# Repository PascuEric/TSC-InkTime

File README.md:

# InkTime — Smartwatch

InkTime is an open-source, minimalist smartwatch built around an always-readable 1.54" e-paper display and optimized for month-class battery life (≥30 days on a 250 mAh LiPo). It features BLE 5.0 notifications, embedded step counting, haptic alerts, and USB-C charging.

---

## Block Diagram

```
                          ┌──────────────────────────────────────────┐
         USB-C            │           nRF52840 (U1)                  │
        ──────►──┐        │                                          │
                 │  VBUS  │  ┌─────────────────────────────────┐     │
                 ▼        │  │         I2C Bus                 │     │
          ┌──────────┐    │  │  SDA P0.06 / SCL P0.07          │     │
          │ BQ25180  │◄───┼──┤  Pull-up 3K3 to 3V3             │     │
          │  (IC1)   │    │  │                                 │     │
          │ Charger  │    │  │  BQ25180 (0x6A)  RT6160 (0x75)  │     │
          └────┬─────┘    │  │  MAX17048 (0x36) BMA421 (0x18)  │     │
               │ SYS      │  │  DRV2605L (0x5A)                │     │
          ┌────▼─────┐    │  └─────────────────────────────────┘     │
          │ RT6160   │◄───┤                                          │
          │  (IC9)   │    │  ┌─────────────────────────────────┐     │
          │Buck-Boost│    │  │        SPI Bus                  │     │
          └────┬─────┘    │  │  SCK P0.02 / MOSI P0.03         │     │
               │ 3V3      │  │  CS P0.05 / DC P0.15            │     │
               ▼          │  │  RST P0.16 / BUSY P0.17         │     │
    ┌──────────────────┐  │  │  PFET gate P1.01                │     │
    │   3V3 Power Rail │  │  │                                 │     │
    └─┬───┬───┬───┬────┘  │  │  E-Paper 1.54" 200x200 (J1)     │     │
      │   │   │   │       │  │  via SI1308EDL MOSFET (Q3)      │     │
      │   │   │   │       │  └─────────────────────────────────┘     │
      │   │   │   │       │                                          │
      │   │   │   │       │  GPIO                                    │
      │   │   │   └───────┼──► SW_UP P0.13 / SW_DN P0.14             │
      │   │   │           │    SW_ENT P1.00                          │
      │   │   │           │  INT: BMA421 INT1→P0.08 INT2→P1.08       │
      │   │   │           │       MAX17048 ALRT→P0.10                │
      │   │   │           │       BQ25180 /INT→P0.11                 │
      │   │   │           │       HAPTIC_EN→P0.12                    │
      │   │   │           │                                          │
      │   │   │           │  RF: ANT→L1(3.9nH)→L3(15nH)→ANT1         │
      │   │   │           │  USB: D+/D-→USBLC6(D3)→USB-C (J4)        │
      │   │   │           │  SWD: SWDIO/SWDCLK/RESET→TC2030 (J2)     │
      │   │   │           └──────────────────────────────────────────┘
      │   │   │
      │   │  ┌▼────────────┐    ┌──────────────┐
      │   │  │  DRV2605L   ├───►│  ERM Motor   │
      │   │  │  (IC2) I2C  │    │  (Haptic)    │
      │   │  └─────────────┘    └──────────────┘
      │   │
      │  ┌▼────────────┐
      │  │   BMA421    │
      │  │   (IC3) I2C │  INT1→P0.08 / INT2→P1.08
      │  └─────────────┘
      │
     ┌▼────────────┐
     │  MAX17048   │
     │  (U3) I2C   │  ALRT→P0.10
     └─────────────┘

  ┌──────────┐
  │  LiPo    │──VBAT──► BQ25180 (BAT) ──► MAX17048 (BAT/VDD)
  │ 250 mAh  │
  └──────────┘
```

---

## Bill of Materials (BOM)

| Qty | Ref | Component | Package | Description | JLCPCB | Datasheet |
|-----|-----|-----------|---------|-------------|--------|-----------|
| 1 | U1 | nRF52840-QIAA-R | aQFN73 | MCU BLE 5.0 + USB 2.0 | — | [Link](https://infocenter.nordicsemi.com/pdf/nRF52840_PS_v1.7.pdf) |
| 1 | IC1 | BQ25180YBGR | DSBGA-8 | LiPo charger / power path | [C3682423](https://jlcpcb.com/partdetail/TexasInstruments-BQ25180YBGR/C3682423) | [Link](https://www.ti.com/lit/ds/symlink/bq25180.pdf) |
| 1 | IC9 | RT6160AWSC | WLCSP-15 | Buck-boost 3.3V regulator | [C7065276](https://jlcpcb.com/partdetail/Richtek-RT6160AWSC/C7065276) | [Link](https://www.richtek.com/assets/product_file/RT6160A/DS6160A-00.pdf) |
| 1 | U3 | MAX17048G+T10 | DFN-8 | Fuel gauge I2C | — | [Link](https://datasheets.maximintegrated.com/en/ds/MAX17048-MAX17049.pdf) |
| 1 | IC3 | BMA421 | LGA-12 | Accelerometer + step counter | — | [Link](https://www.bosch-sensortec.com/media/boschsensortec/downloads/datasheets/bst-bma421-ds000.pdf) |
| 1 | IC2 | DRV2605YZFR | DSBGA-9 | Haptic driver ERM/LRA | — | [Link](https://www.ti.com/lit/ds/symlink/drv2605l.pdf) |
| 1 | Q3 | SI1308EDL-T1-GE3 | SC-70 | N-ch MOSFET EPD power gate | — | [Link](https://www.vishay.com/docs/63587/si1308edl.pdf) |
| 1 | DMG2305UX-7 | DMG2305UX-7 | SOT-23 | P-ch MOSFET EPD drive | — | — |
| 1 | ANT1 | 2450AT18B100E | SMD 3216 | 2.45 GHz chip antenna | — | [Link](https://www.johansontechnology.com/datasheets/2450AT18B100E/2450AT18B100E.pdf) |
| 1 | J4 | KH-TYPE-C-16P | THT | USB-C 16-pin connector | — | — |
| 1 | D3 | USBLC6-2SC6Y | SOT-23-6 | USB ESD protection | — | [Link](https://www.st.com/resource/en/datasheet/usblc6-2.pdf) |
| 3 | D2,D4,D5 | MBR0530 | SOD-123 | Schottky diode 30V 500mA | — | — |
| 1 | J2 | TC2030-IDC | PCB footprint | Tag-Connect SWD debug | — | [Link](https://www.tag-connect.com/wp-content/uploads/bsk-pdf-manager/TC2030-IDC_1.pdf) |
| 1 | J1 | 503480-2400 | FPC 24-pin | E-paper FPC connector 0.5mm | — | [Mouser](https://www.mouser.co.uk/ProductDetail/Molex/503480-2400) |
| 3 | SW_UP,SW_DN,SW_ENT | EVP-AKE31A | SMD | Tactile button Panasonic | — | — |
| 1 | X1 | 32 MHz crystal | 2016 SMD | HFXO nRF52840 | — | — |
| 1 | X2 | 32.768 kHz crystal | 3215 SMD | LFXO RTC nRF52840 | — | — |
| 1 | L7 | FTC252012SR47MBCA | 2520 | 0.47 µH RT6160 switching | [C5832368](https://jlcpcb.com/partdetail/6763488-FTC252012SR47MBCA/C5832368) | — |
| 1 | L2 | 10 µH | 0402 | RT6160 power stage | — | — |
| 1 | L3 | 15 nH | 0402 | RF matching network | — | — |
| 1 | L1 | 3.9 nH | 0402 | RF matching network | — | — |
| 1 | L5 | 68 µH | 0402 | EPD boost converter | — | — |
| 5 | C5,C7,C8,C12,C19 | 100 nF | 0201 | Decoupling nRF52840 | — | — |
| 4 | C1,C2,C17,C18 | 12 pF | 0201 | Crystal load caps | — | — |
| 6 | C29–C32,C37,C38 | 1 µF | 0201 | Bulk decoupling | — | — |
| 3 | C23,C27,C42 | 0.1 µF | 0201 | Decoupling | — | — |
| 2 | C25,C33 | 22 µF | 0402 | RT6160 output caps | — | — |
| 3 | C14,C20,C21 | 4.7 µF | 0402 | Bulk decoupling | — | — |
| 1 | C43 | 4.7 µF | 0402 | DECUSB nRF52840 | — | — |
| 1 | C24 | 10 µF | 0402 | RT6160 input cap | — | — |
| 9 | EPD_C1..C12 | 1 µF/50V | 0402 | EPD supply caps | — | — |
| 1 | C15 | 1.0 µF | 0201 | DEC4/6 nRF52840 | — | — |
| 1 | C11 | 100 pF | 0201 | RF matching | — | — |
| 2 | C3,C4 | 1 pF | 0201 | RF matching | — | — |
| 1 | C9 | 820 pF | 0201 | RF decoupling | — | — |
| 2 | R17,R18 | 3.3 kΩ | 0201 | I2C pull-ups SDA/SCL | — | — |
| 3 | R5,R7,R8 | 10 kΩ | 0201 | Button pull-ups | — | — |
| 2 | R1_USB,R2_USB | 5.1 kΩ | 0201 | USB CC1/CC2 resistors | — | — |
| 14 | TP_* | Test pad | TP20R | Test points | — | — |
| 1 | SJ1 | Solder jumper | SMD | Config jumper | — | — |

---

## Hardware Functionality Description

### Power Architecture

```
USB 5V → BQ25180 (IN) → BQ25180 (SYS) → RT6160 (VIN) → 3.3V rail
LiPo   → BQ25180 (BAT) and LiPo → MAX17048 (BAT/VDD)
```

**BQ25180 (IC1)** handles LiPo charging and power-path management. When USB is present, it powers the system from USB and charges the battery simultaneously without brownout on connect/disconnect. TS/MR strapped to GND (R9, 10kΩ) for Rev A. Decoupling: C37 (1µF on IN), C39 (10µF on SYS), C38 (1µF on BAT).

**RT6160 (IC9)** is a buck-boost maintaining stable 3.3V across the full LiPo discharge range (4.2V → 3.0V). VSEL tied low for 3.3V output. EN tied to VSYS (always on when SYS present). Switching inductor L7 (0.47µH) placed close to SW pins. Output caps C25 + C33 (22µF each).

**MAX17048 (U3)** reports battery state-of-charge over I2C (0x36) using the ModelGauge algorithm, requiring no sense resistor. ALRT output (active-low) on P0.10 wakes MCU when battery drops below threshold.

### MCU — nRF52840 (U1)

ARM Cortex-M4F, 64 MHz, BLE 5.0, USB 2.0 Full Speed. Normal-voltage mode (VDD = 3.3V). Internal DC/DC regulator (REG1) enabled in firmware to reduce active-mode current.

Decoupling placed directly at MCU pins: DEC1 → C7 (100nF), DEC3 → C8 (100nF), DEC4/DEC6 → C15 (1µF), DECUSB → C43 (4.7µF). DC/DC network: DCC → L2 (10µH) → L3 (15nH) → DEC4/6 node.

### I2C Bus

SDA P0.06 / SCL P0.07, pull-ups R17+R18 (3.3kΩ to 3V3), 100 kHz default.

| Device | Address | Function |
|--------|---------|---------|
| BMA421 (IC3) | 0x18 | Accelerometer + step counter |
| MAX17048 (U3) | 0x36 | Fuel gauge |
| DRV2605L (IC2) | 0x5A | Haptic driver |
| BQ25180 (IC1) | 0x6A | Charger / power path |
| RT6160 (IC9) | 0x75 | Buck-boost regulator |

### E-Paper Display (J1)

1.54" 200×200 e-paper via Molex 503480-2400 24-pin FPC connector (0.5mm pitch). SPI communication. VEPD switched by SI1308EDL N-ch MOSFET (Q3, gate P1.01) for complete power gating between updates. EPD boost circuit: D2, D4, D5 (MBR0530) + L5 (68µH) + DMG2305UX-7 generates PREVGL/PREVGH panel voltages. Optional DNP series resistors on SPI lines prevent back-powering when VEPD off.

### Accelerometer — BMA421 (IC3)

Embedded step counter running autonomously. I2C 0x18 (CSB high, SDO low). INT1 → P0.08 for motion/step wake; INT2 → P1.08 for secondary events. Placed away from ERM motor to avoid false motion coupling.

### Haptics — DRV2605L (IC2)

Drives ERM motor via I2C (0x5A). EN pin P0.12 shuts down driver completely between events. Built-in waveform library selectable by effect ID over I2C.

### RF — ANT1

Matching network: ANT → L1 (3.9nH) → L3 (15nH) → C3/C4 (1pF to GND) → 2450AT18B100E chip antenna. Antenna at PCB edge with physical cutout and GND keepout underneath.

### USB-C (J4)

USB 2.0 FS. D+/D- differential pair with matched lengths. USBLC6-2SC6Y (D3) ESD protection at connector entry. R1_USB + R2_USB (5.1kΩ each) on CC1/CC2 for USB-C sink detection.

### Energy Budget

| Condition | Current | Fraction | Avg µA |
|-----------|---------|----------|--------|
| Deep sleep | ~3 µA | 98.8% | ~3.0 |
| EPD partial refresh (2s/min) | ~8 mA | 0.13% | ~10.4 |
| BLE notification | ~15 mA | 0.05% | ~7.5 |
| Haptic event | ~50 mA | 0.02% | ~10.0 |
| **Total** | | | **~31 µA** |

250 mAh / 0.031 mA ≈ **~33 days** typical use.

---

## nRF52840 Pin Assignment

| Pin | Net | Dir | Connected to | Rationale |
|-----|-----|-----|-------------|-----------|
| P0.02 | SCK | OUT | EPD display | SPI — high-speed Port 0 peripheral |
| P0.03 | MOSI | OUT | EPD display | SPI data out |
| P0.05 | EPD_CS | OUT | EPD display | SPI chip select |
| P0.06 | SDA | I/O | All I2C ICs | Nordic reference I2C pin |
| P0.07 | SCL | OUT | All I2C ICs | Nordic reference I2C pin |
| P0.08 | IMU_INT1 | IN | BMA421 INT1 | GPIO sense, wake from deep sleep |
| P0.10 | ALERT | IN | MAX17048 ALRT | Low battery wake |
| P0.11 | PMIC_INT | IN | BQ25180 /INT | Charger event interrupt |
| P0.12 | HAPTIC_EN | OUT | DRV2605L EN | Haptic driver shutdown between events |
| P0.13 | SW_UP | IN | Button UP | GPIO sense + internal pull-up, wake capable |
| P0.14 | SW_DN | IN | Button DOWN | GPIO sense + internal pull-up, wake capable |
| P0.15 | EPD_DC | OUT | EPD display | Data/command select |
| P0.16 | EPD_RST | OUT | EPD display | Panel reset |
| P0.17 | EPD_BUSY | IN | EPD display | Busy status |
| P0.18/RESET | nRESET | IN | TC2030 pin 6 | Dedicated hardware reset |
| P0.00/XL1 | LFXO | — | X2 crystal | 32.768 kHz RTC |
| P0.01/XL2 | LFXO | — | X2 crystal | 32.768 kHz RTC |
| XC1/XC2 | HFXO | — | X1 crystal | 32 MHz RF/CPU |
| ANT | RF | — | L1→L3→ANT1 | Antenna matching network |
| VBUS | Detect | IN | USB-C VBUS | USB attach detection |
| D+/D- | USB | I/O | USBLC6→J4 | USB 2.0 FS differential pair |
| SWDIO | SWD | I/O | TC2030 pin 2 | Programming + debug |
| SWDCLK | SWD | IN | TC2030 pin 4 | Programming + debug |
| P1.00 | SW_ENT | IN | Button ENTER | GPIO sense + pull-up, wake capable |
| P1.01 | EPD_PWR | OUT | Q3 gate | EPD power gate control |
| P1.08 | IMU_INT2 | IN | BMA421 INT2 | Secondary accel events |
| DCC | DC/DC | — | L2 (10µH) | Internal regulator inductor |
| DEC1 | Decoupling | — | C7 (100nF) | Core decoupling |
| DEC3 | Decoupling | — | C8 (100nF) | Core decoupling |
| DEC4/DEC6 | Decoupling | — | C15 (1µF) | DC/DC output node |
| DECUSB | Decoupling | — | C43 (4.7µF) | USB PHY decoupling |

---

## PCB Design Notes

**Stackup:** 2-layer, FR4, 1.6mm. Top + Bottom copper (1oz), green soldermask, white silkscreen.

**Placement:** nRF52840 centered; RF matching + ANT1 at top-right board edge with physical PCB cutout and GND keepout under antenna; BQ25180 + RT6160 grouped away from antenna; BMA421 separated from ERM motor; all 100nF decoupling within 0.5mm of VDD pins; TC2030 at board edge.

**Trace widths:** Power (3V3, VBAT) = 0.3mm; signals (SPI, I2C, GPIO) ≥ 0.15mm; USB D+/D- = 0.15mm matched length. No 90° angles.

**GND:** Polygon on Top + Bottom layers, via stitching throughout, especially dense around RF section.

---

## Repository Structure

```
├── Hardware/
│   ├── schemTSC.sch
│   └── schemaPCB.brd
├── Manufacturing/
│   ├── gerbers.zip
│   ├── bom.csv
│   └── pick-n-place.csv
├── Mechanical/
│   ├── casedPCB.step
│   └── exploded_case.step
├── Images/
│   ├── exploded_render.png
│   ├── PCB_render.png
│   ├── PCB_top.png
│   └── PCB_bottom.png
├── LICENSE
└── README.md
```

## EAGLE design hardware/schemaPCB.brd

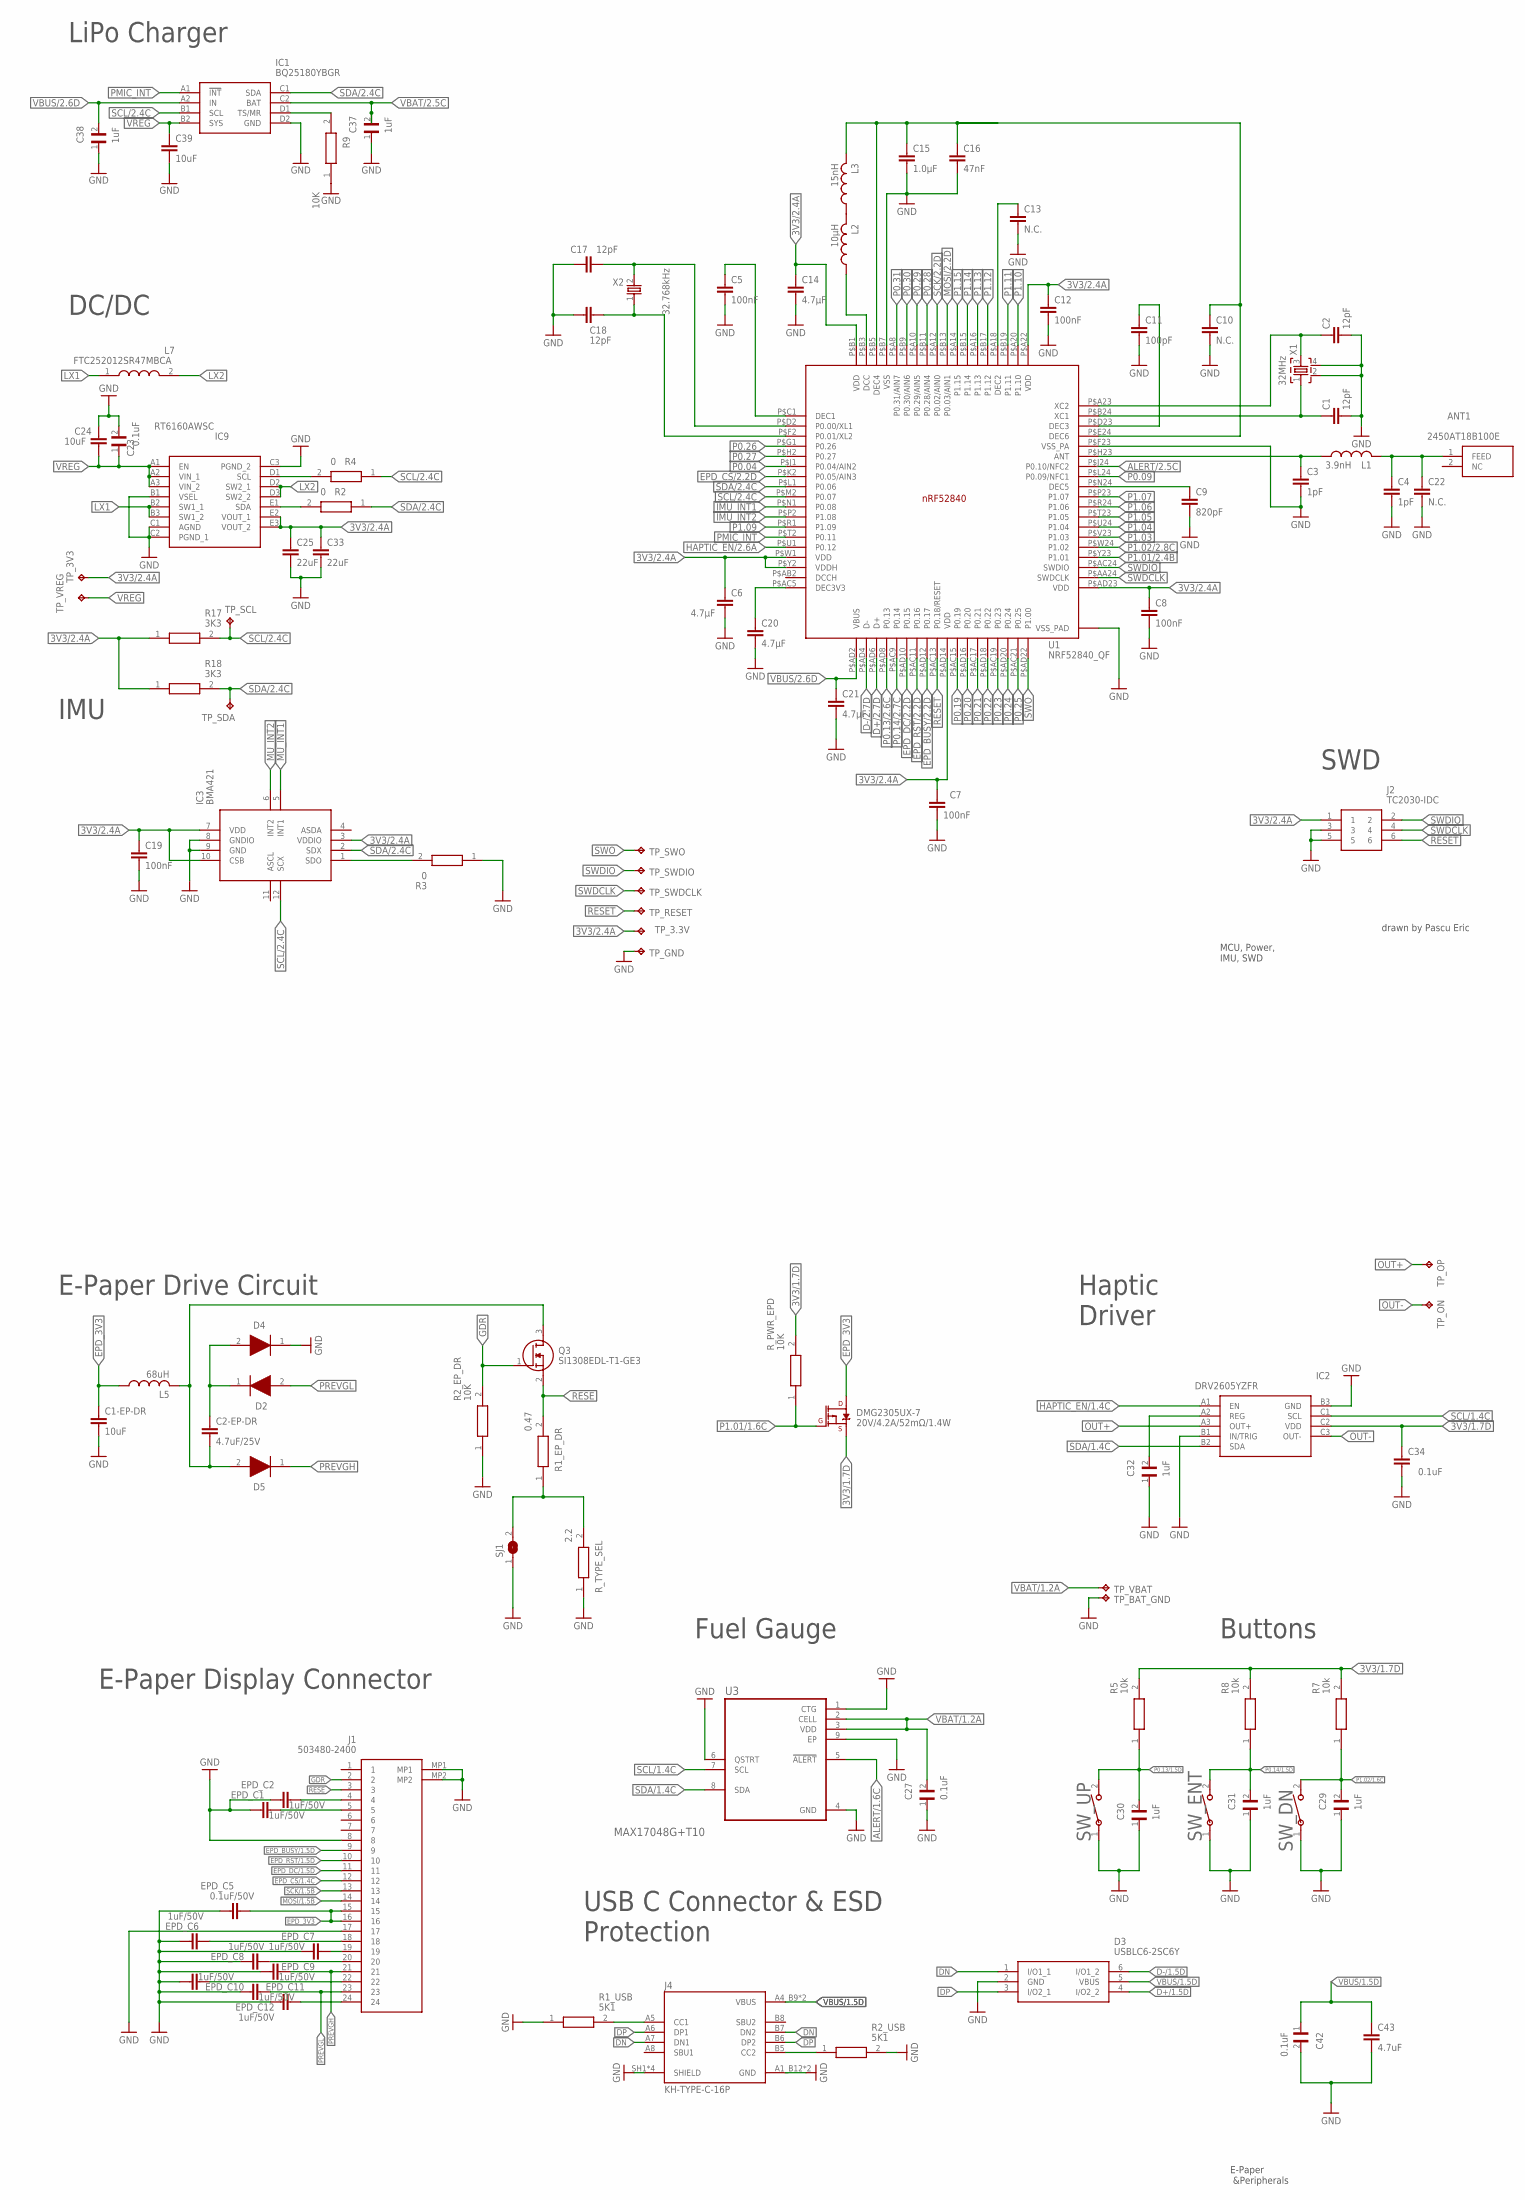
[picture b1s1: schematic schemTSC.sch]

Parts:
ANT1: 2450AT18B100E; 2450AT18B100E_ANTC3216X140N
C1, C2, C17, C18: 12pF; NORDIC_NRF_3_RESC0201_L
C1-EP-DR, C39: 10uF; NORDIC_NRF_3_RESC0201_L
C2-EP-DR: 4.7uF/25V; NORDIC_NRF_3_RESC0201_L
C3, C4: 1pF; NORDIC_NRF_3_RESC0201_L
C5, C7, C8, C12, C19: 100nF; NORDIC_NRF_3_RESC0201_L
C6: 4.7µF; NORDIC_NRF_3_RESC0201_L
C9: 820pF; NORDIC_NRF_3_RESC0201_L
C10, C13, C22: N.C.; NORDIC_NRF_3_RESC0201_L
C11: 100pF; NORDIC_NRF_3_RESC0201_L
C14, C20, C21: 4.7µF; ESP32_C6_LIBRARY_1_ESP32_WROVER_EAGLE-LTSPICE_C0402
C15: 1.0µF; NORDIC_NRF_3_RESC0201_L
C16: 47nF; NORDIC_NRF_3_RESC0201_L
C23, C27, C42: 0.1uF; GRM011R60J152KE01L_2_CAPC0201X13N
C24: 10uF; ESP32_C6_LIBRARY_1_ESP32_WROVER_EAGLE-LTSPICE_C0402
C25, C33: 22uF; ESP32_C6_LIBRARY_1_ESP32_WROVER_EAGLE-LTSPICE_C0402
C29, C30, C31, C32, C37, C38: 1uF; GRM011R60J152KE01L_2_CAPC0201X13N
C34: 0.1uF; NORDIC_NRF_3_RESC0201_L
C43: 4.7uF; ESP32_C6_LIBRARY_1_ESP32_WROVER_EAGLE-LTSPICE_C0402
D2, D4, D5: ESP32_C6_LIBRARY_5_MBR0530; ESP32_C6_LIBRARY_5_SOD3716X135N
D3: USBLC6-2SC6Y; ESP32_C6_LIBRARY_3_SOT95P280X145-6N
DMG2305UX-7: 20V/4.2A/52mΩ/1.4W; ESP32_C6_LIBRARY_4_ESP32_C6_LIBRARY_4_ESP32_C6_LIBRARY_4_ES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
EPD_C1, EPD_C2, EPD_C6, EPD_C7, EPD_C8, EPD_C9, EPD_C10, EPD_C11, EPD_C12: 1uF/50V; ESP32_C6_LIBRARY_1_ESP32_WROVER_EAGLE-LTSPICE_C0402
EPD_C5: 0.1uF/50V; ESP32_C6_LIBRARY_1_ESP32_WROVER_EAGLE-LTSPICE_C0402
IC1: BQ25180YBGR; BQ25180YBGR_BGA8C40P2X4_100X155X50
IC2: DRV2605YZFR; DRV2605YZFR_BGA9C50P3X3_144X144X62
IC3: BMA421; BMA423_BMA423
IC9: RT6160AWSC; RT6160AWSC_BGA15C40P3X5_140X230X60
J1: 503480-2400; 503480-2400_5034802400
J2: TC2030-IDC; TC2030-IDC_TC2030IDC
J4: KH-TYPE-C-16P; KH-TYPE-C-16P_KINGHELM_KH-TYPE-C-16P
L1: 3.9nH; NORDIC_NRF_2_RESC0402_L
L2: 10µH; NORDIC_NRF_2_RESC0402_L
L3: 15nH; NORDIC_NRF_2_RESC0402_L
L5: 68uH; NORDIC_NRF_2_RESC0402_L
L7: FTC252012SR47MBCA; MLP2016SR47MT0S1_INDC2016X100N
Q3: SI1308EDL-T1-GE3; ESP32_C6_LIBRARY_6_SOT65P210X110-3N
R1_EP_DR: 0.47; ERA-1AEB3401C_0201
R1_USB: 5K1; CPF0201D7K68C1_0201
R2, R4: 0; CPF0201D7K68C1_0201
R2_EP_DR, R9: 10K; ERA-1AEB3401C_0201
R2_USB: 5K1; ERA-1AEB3401C_0201
R3: 0; ERA-1AEB3401C_0201
R5, R7, R8: 10k; CPF0201D7K68C1_0201
R17, R18: 3K3; CPF0201D7K68C1_0201
R_PWR_EPD: 10K; CPF0201D7K68C1_0201
R_TYPE_SEL: 2.2; ERA-1AEB3401C_0201
SJ1: ESP32_C6_LIBRARY_7_JUMPER_SJ
SW_DN: 2025-10-22_07-23-44_LIBRARY_EVP-AKE31ASW_EVP-AKE3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; 2025-10-22_07-23-44_LIBRARY_SW_EVP-AKE31A_PAN
SW_ENT: 2025-10-22_07-23-44_LIBRARY_EVP-AKE31ASW_EVP-AKE3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; 2025-10-22_07-23-44_LIBRARY_SW_EVP-AKE31A_PAN
SW_UP: 2025-10-22_07-23-44_LIBRARY_EVP-AKE31ASW_EVP-AKE3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; 2025-10-22_07-23-44_LIBRARY_SW_EVP-AKE31A_PAN
TP_3.3V, TP_3V3: HECTOR_WATCH_1_TPTP20R; HECTOR_WATCH_1_TP20R
TP_BAT_GND: HECTOR_WATCH_1_TPTP20R; HECTOR_WATCH_1_TP20R
TP_GND: HECTOR_WATCH_1_TPTP20R; HECTOR_WATCH_1_TP20R
TP_ON: HECTOR_WATCH_1_TPTP20R; HECTOR_WATCH_1_TP20R
TP_OP: HECTOR_WATCH_1_TPTP20R; HECTOR_WATCH_1_TP20R
TP_RESET: HECTOR_WATCH_1_TPTP20R; HECTOR_WATCH_1_TP20R
TP_SCL: HECTOR_WATCH_1_TPTP20R; HECTOR_WATCH_1_TP20R
TP_SDA: HECTOR_WATCH_1_TPTP20R; HECTOR_WATCH_1_TP20R
TP_SWDCLK: HECTOR_WATCH_1_TPTP20R; HECTOR_WATCH_1_TP20R
TP_SWDIO: HECTOR_WATCH_1_TPTP20R; HECTOR_WATCH_1_TP20R
TP_SWO: HECTOR_WATCH_1_TPTP20R; HECTOR_WATCH_1_TP20R
TP_VBAT: HECTOR_WATCH_1_TPTP20R; HECTOR_WATCH_1_TP20R
TP_VREG: HECTOR_WATCH_1_TPTP20R; HECTOR_WATCH_1_TP20R
U1: NRF52840_QF; NORDIC_NRF_4_AQFN50P700X700X85_HS-74N
U3: MAX17048G+T10; ESP32_C6_LIBRARY_SON50P200X200X80-9N
X1: 32MHz; NORDIC_NRF_BT-XTAL_2016_N
X2: 32.768kHz; NORDIC_NRF_1_XTAL_3215_N

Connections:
3V3/1.7D: C34.1, DMG2305UX-7.2 (S), IC2.C2 (VDD), R5.2, R7.2, R8.2, R_PWR_EPD.2
3V3/2.4A: C6.1, C7.1, C8.1, C12.1, C14.1, C19.1, C25.1, C33.1, IC3.3 (VDDIO), IC3.7 (VDD), IC3.10 (CSB), IC9.E2 (VOUT_1), IC9.E3 (VOUT_2), J2.1, R17.1, R18.1, TP_3.3V.TP, TP_3V3.TP, U1.P$A22 (VDD), U1.P$AD14 (VDD), U1.P$AD23 (VDD), U1.P$B1 (VDD), U1.P$W1 (VDD), U1.P$Y2 (VDDH)
ALERT/1.6C: U3.5 (!ALERT)
ALERT/2.5C: U1.P$J24 (P0.10/NFC2)
D+/1.5D: D3.4 (I/O2_2)
D+/2.7D: U1.P$AD6 (D+)
D-/1.5D: D3.6 (I/O1_2)
D-/2.7D: U1.P$AD4 (D-)
DN: D3.1 (I/O1_1), J4.A7 (DN1), J4.B7 (DN2)
DP: D3.3 (I/O2_1), J4.A6 (DP1), J4.B6 (DP2)
EPD_3V3: C1-EP-DR.1, DMG2305UX-7.3 (D), EPD_C5.2, J1.15, J1.16, L5.1
EPD_BUSY/1.5D: J1.9
EPD_BUSY/2.2D: U1.P$AD12 (P0.17)
EPD_CS/1.4C: J1.12
EPD_CS/2.2D: U1.P$K2 (P0.05/AIN3)
EPD_DC/1.5D: J1.11
EPD_DC/2.2D: U1.P$AD10 (P0.15)
EPD_RST/1.5D: J1.10
EPD_RST/2.2D: U1.P$AC11 (P0.16)
GDR: J1.2, Q3.1 (G), R2_EP_DR.2
GND: C1.2, C1-EP-DR.2, C2.2, C3.2, C4.2, C5.2, C6.2, C7.2, C8.2, C9.2, C10.2, C11.2, C12.2, C13.2, C14.2, C15.2, C16.2, C17.1, C18.2, C19.2, C20.2, C21.2, C22.2, C23.2, C24.1, C25.2, C27.1, C29.1, C30.1, C31.1, C32.1, C33.2, C34.2, C37.1, C38.1, C39.2, C42.2, C43.2, D3.2 (GND), D4.1 (K), EPD_C1.1, EPD_C2.1, EPD_C5.1, EPD_C6.1, EPD_C7.1, EPD_C8.1, EPD_C9.1, EPD_C10.1, EPD_C11.1, EPD_C12.1, IC1.D2 (GND), IC2.B1 (IN/TRIG), IC2.B3 (GND), IC3.8 (GNDIO), IC3.9 (GND), IC9.B1 (VSEL), IC9.C1 (AGND), IC9.C2 (PGND_1), IC9.C3 (PGND_2), J1.8, J1.17, J1.MP1, J1.MP2, J2.3, J2.5, J4.A1_B12 (GND), J4.A12_B1 (GND), J4.SH1 (SHIELD), J4.SH2 (SHIELD), J4.SH3 (SHIELD), J4.SH4 (SHIELD), R1_USB.1, R2_EP_DR.1, R2_USB.2, R3.1, R9.1, R_TYPE_SEL.1, SJ1.1, SW_DN.1, SW_ENT.1, SW_UP.1, TP_BAT_GND.TP, TP_GND.TP, U1.P$74 (VSS_PAD), U1.P$75 (VSS_PAD), U1.P$76 (VSS_PAD), U1.P$77 (VSS_PAD), U1.P$78 (VSS_PAD), U1.P$79 (VSS_PAD), U1.P$80 (VSS_PAD), U1.P$81 (VSS_PAD), U1.P$82 (VSS_PAD), U1.P$83 (VSS_PAD), U1.P$84 (VSS_PAD), U1.P$85 (VSS_PAD), U1.P$86 (VSS_PAD), U1.P$87 (VSS_PAD), U1.P$88 (VSS_PAD), U1.P$89 (VSS_PAD), U1.P$90 (VSS_PAD), U1.P$B7 (VSS), U1.P$F23 (VSS_PA), U3.1 (CTG), U3.4 (GND), U3.6 (QSTRT), U3.9 (EP), X1.2, X1.4
HAPTIC_EN/1.4C: IC2.A1 (EN)
HAPTIC_EN/2.6A: U1.P$U1 (P0.12)
IMU_INT1: U1.P$N1 (P0.08)
IMU_INT2: U1.P$P2 (P1.08)
JJ: C10.1, C15.1, C16.1, L3.2, U1.P$B5 (DEC4), U1.P$E24 (DEC6)
LX1: IC9.B2 (SW1_1), IC9.B3 (SW1_2), L7.1
LX2: IC9.D2 (SW2_1), IC9.D3 (SW2_2), L7.2
MOSI/1.5B: J1.14
MOSI/2.2D: U1.P$B13 (P0.03/AIN1)
MU_INT1: IC3.5 (INT1)
MU_INT2: IC3.6 (INT2)
unnamed: IC1.D1 (TS/MR), R9.2
unnamed: IC9.D1 (SCL), R4.2
unnamed: IC9.E1 (SDA), R2.2
unnamed: IC3.1 (SDO), R3.2
unnamed: C20.1, U1.P$AC5 (DEC3V3)
unnamed: C18.1, U1.P$F2 (P0.01/XL2), X2.1
unnamed: C17.2, U1.P$D2 (P0.00/XL1), X2.2
unnamed: C5.1, U1.P$C1 (DEC1)
unnamed: C9.1, U1.P$N24 (DEC5)
unnamed: L2.1, U1.P$B3 (DCC)
unnamed: L2.2, L3.1
unnamed: C3.1, L1.1, U1.P$H23 (ANT)
unnamed: ANT1.1 (FEED), C4.1, C22.1, L1.2
unnamed: C11.1, U1.P$D23 (DEC3)
unnamed: C2.1, U1.P$A23 (XC2), X1.3
unnamed: C1.1, U1.P$B24 (XC1), X1.1
unnamed: C2-EP-DR.1, D2.1 (K), D4.2 (A)
unnamed: R1_EP_DR.1, R_TYPE_SEL.2, SJ1.2
unnamed: C2-EP-DR.2, D5.2 (A), L5.2, Q3.3 (D)
unnamed: C13.1, U1.P$A18 (DEC2)
unnamed: C32.2, IC2.A2 (REG)
unnamed: EPD_C2.2, J1.4
unnamed: EPD_C1.2, J1.5
unnamed: EPD_C6.2, J1.18
unnamed: EPD_C7.2, J1.19
unnamed: EPD_C8.2, J1.20
unnamed: J4.A5 (CC1), R1_USB.2
unnamed: EPD_C10.2, J1.22
unnamed: EPD_C12.2, J1.24
unnamed: J4.B5 (CC2), R2_USB.1
OUT+: IC2.A3 (OUT+), TP_OP.TP
OUT-: IC2.C3 (OUT-), TP_ON.TP
P0.04: U1.P$J1 (P0.04/AIN2)
P0.09: U1.P$L24 (P0.09/NFC1)
P0.13/1.5D: C30.2, R5.1, SW_UP.2
P0.13/2.6C: U1.P$AD8 (P0.13)
P0.14/1.5D: C31.2, R8.1, SW_ENT.2
P0.14/2.7C: U1.P$AC9 (P0.14)
P0.19: U1.P$AC15 (P0.19)
P0.20: U1.P$AD16 (P0.20)
P0.21: U1.P$AC17 (P0.21)
P0.22: U1.P$AD18 (P0.22)
P0.23: U1.P$AC19 (P0.23)
P0.24: U1.P$AD20 (P0.24)
P0.25: U1.P$AC21 (P0.25)
P0.26: U1.P$G1 (P0.26)
P0.27: U1.P$H2 (P0.27)
P0.28: U1.P$B11 (P0.28/AIN4)
P0.29: U1.P$A10 (P0.29/AIN5)
P0.30: U1.P$B9 (P0.30/AIN6)
P0.31: U1.P$A8 (P0.31/AIN7)
P1.01/1.6C: DMG2305UX-7.1 (G), R_PWR_EPD.1
P1.01/2.4B: U1.P$Y23 (P1.01)
P1.02/1.6C: C29.2, R7.1, SW_DN.2
P1.02/2.8C: U1.P$W24 (P1.02)
P1.03: U1.P$V23 (P1.03)
P1.04: U1.P$U24 (P1.04)
P1.05: U1.P$T23 (P1.05)
P1.06: U1.P$R24 (P1.06)
P1.07: U1.P$P23 (P1.07)
P1.09: U1.P$R1 (P1.09)
P1.10: U1.P$A20 (P1.10)
P1.11: U1.P$B19 (P1.11)
P1.12: U1.P$B17 (P1.12)
P1.13: U1.P$A16 (P1.13)
P1.14: U1.P$B15 (P1.14)
P1.15: U1.P$A14 (P1.15)
PMIC_INT: IC1.A1 (!INT), U1.P$T2 (P0.11)
PREVGH: D5.1 (K), EPD_C9.2, J1.21
PREVGL: D2.2 (A), EPD_C11.2, J1.23
RESE: J1.3, Q3.2 (S), R1_EP_DR.2
RESET: J2.6, TP_RESET.TP, U1.P$AC13 (P0.18/RESET)
SCK/1.5B: J1.13
SCK/2.2D: U1.P$A12 (P0.02/AIN0)
SCL/1.4C: IC2.C1 (SCL), U3.7 (SCL)
SCL/2.4C: IC1.B1 (SCL), IC3.12 (SCX), R4.1, R17.2, TP_SCL.TP, U1.P$M2 (P0.07)
SDA/1.4C: IC2.B2 (SDA), U3.8 (SDA)
SDA/2.4C: IC1.C1 (SDA), IC3.2 (SDX), R2.1, R18.2, TP_SDA.TP, U1.P$L1 (P0.06)
SWDCLK: J2.4, TP_SWDCLK.TP, U1.P$AA24 (SWDCLK)
SWDIO: J2.2, TP_SWDIO.TP, U1.P$AC24 (SWDIO)
SWO: TP_SWO.TP, U1.P$AD22 (P1.00)
VBAT/1.2A: C27.2, TP_VBAT.TP, U3.2 (CELL), U3.3 (VDD)
VBAT/2.5C: C37.2, IC1.C2 (BAT)
VBUS/1.5D: C42.1, C43.1, D3.5 (VBUS), J4.A4_B9 (VBUS), J4.A9_B4 (VBUS)
VBUS/2.6D: C21.1, C38.2, IC1.A2 (IN), U1.P$AD2 (VBUS)
VREG: C23.1, C24.2, C39.1, IC1.B2 (SYS), IC9.A1 (EN), IC9.A2 (VIN_1), IC9.A3 (VIN_2), TP_VREG.TP

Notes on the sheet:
LiPo Charger
DC/DC
IMU
SWD
MCU, Power, IMU, SWD
E-Paper Drive Circuit
Haptic Driver
E-Paper Display Connector
Fuel Gauge
Buttons
E-Paper &Peripherals
USB C Connector & ESD Protection
drawn by Pascu Eric

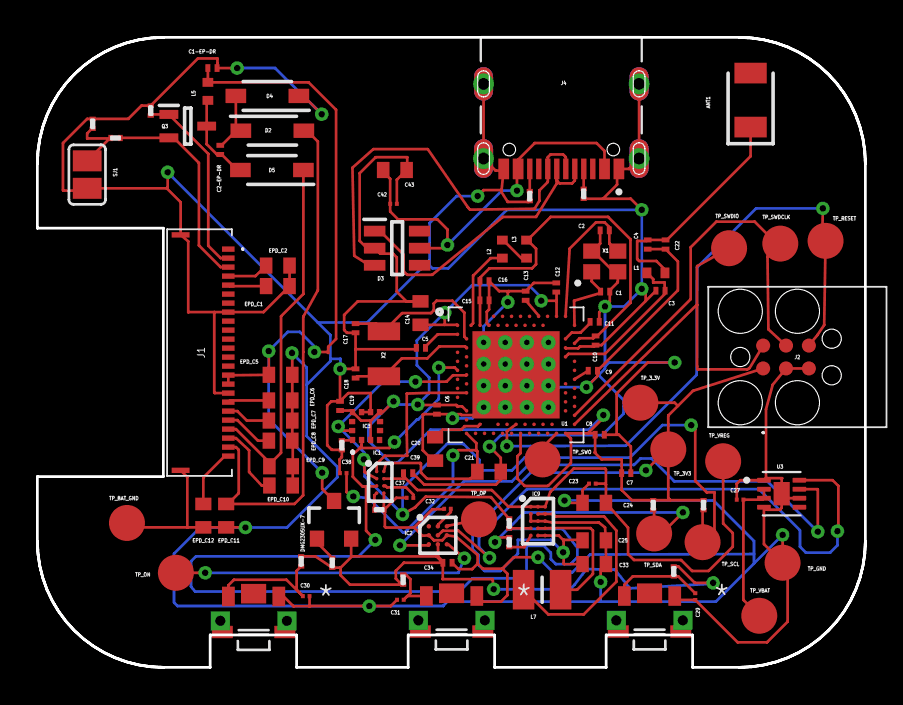
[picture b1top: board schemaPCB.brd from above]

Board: 2 copper layers, 46.0 x 35.0 mm, 105 parts (0 on the bottom side), 63 nets.

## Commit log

2026-04-20 Loaded all finished files
2026-04-20 Added LINCESE

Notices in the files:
parts and their libraries:
InkTime_v5: COPYRIGHT: Copyright (C) 2025 Ultra Librarian. All rights reserved.
